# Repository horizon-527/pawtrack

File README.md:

# PawTrack

宠物独立联网定位器 + 微信小程序。目标：项圈设备获取 GNSS 位置，通过 4G 回传，主人在微信中查看位置和运动轨迹。

**当前状态：软件与可编译硬件原型已建立；尚未完成实体板定位、真实微信登录、公网部署及佩戴验收。**

新增 [定制硬件 EVT-A1 交厂包](hardware/custom/evt-a1/README.md)：可编辑原理图、四层布线 PCB、BOM、Gerber/钻孔/贴片坐标、外壳 STL、Air780EGH 应用和36项实体验收表。ERC/DRC/原理图与 PCB 一致性检查通过；制造发布状态 **HOLD**，先由方案商关闭引脚资料矛盾、电源和叠层评审，再做两台样机。该方案由厂商代采、贴片、装配，详见 [交厂说明](hardware/custom/evt-a1/factory-handoff.md)。

## 已实现
- 微信小程序地图、实时刷新、按日期查询轨迹、坐标转换、轨迹缺口分段。
- 微信登录接口、设备绑定、用户设备隔离、在线/定位过期状态、寻找模式请求与设备确认。
- FastAPI + SQLite 服务，独立设备密钥、一次性绑定码、会话过期/撤销、限流、数据删除与30天保留。
- ESP-IDF v5.4.2 固件：SIM7670G AT通信、GNSS读取、HTTPS上传、NVS缓存、模式心跳；ESP32-S3构建通过。
- 设备模拟器、GNSS日志回放、设备初始化、备份恢复工具、Docker/Caddy配置、CI。

## 先体验小程序
微信开发者工具导入 `miniprogram/`。默认使用游客 AppID 和模拟路线，明确标记演示数据。演示无需真实硬件、服务器或微信登录。
正式接入必须替换 AppID 和 HTTPS 服务地址；项目未使用其他项目的 AppID 或密钥。

## 本地运行与验证
```sh
python3 -m venv work/venv
work/venv/bin/pip install -r requirements.lock.txt
work/venv/bin/python tools/check.py
work/venv/bin/uvicorn server.production:create_app --factory --host 127.0.0.1 --port 8788 --no-access-log
```
不配置真实微信密钥时，登录返回“尚未配置”，不会伪造用户身份。接口测试使用隔离的微信响应替身，不代表真实微信认证通过。

## 文档入口
- **[从采购到真实定位：逐步操作指南](docs/getting-started.md)**
- [完整采购和组装](hardware/procurement-and-assembly.md)
- [真机实测与验收表](docs/acceptance.md)
- [常见问题排查](docs/troubleshooting.md)
- [实施与验收计划](docs/plan.md)
- [硬件采购路线](hardware/README.md)
- [固件配置与烧录](firmware/espidf/README.md)
- [服务部署和备份](deploy/README.md)
- [API v1](docs/api-v1.md)
- [测试记录与待办](docs/verification.md)
- [上线门槛](docs/release.md)
- [开源许可](THIRD_PARTY.md)

## 最新完善
支持继续添加另一只宠物，位置5秒轮询/轨迹30秒缓存刷新、手动刷新、历史轨迹终点、会话过期处理；已在微信开发者工具运行并修复坐标库兼容和地图标记渲染问题。
提供独立真机项目配置工具、部署健康/TLS检查、每日自动备份与7天清理、离线恢复、私有TLS负例测试服务。正式微信登录、实体GNSS/4G与佩戴仍须按验收表测试。

## 原始本地原型
`python3 server/app.py`（8787）与 `python3 tools/simulate.py` 为早期本机开发原型；仅监听本机，固定开发令牌，不可公网部署。它的数据库与 v1 独立。
小程序 `config.js` 可切换 apiMode=prototype 且 apiBase 改为8787进行旧版联调；正式流程保持v1。

## 完成产品仍需的外部条件
实体开发板与SIM；小程序AppID/Secret；可部署的服务器/域名；实际定位、TLS证书验证、功耗及佩戴测试。开发板用于桌面验证，不能直接作为宠物项圈成品。

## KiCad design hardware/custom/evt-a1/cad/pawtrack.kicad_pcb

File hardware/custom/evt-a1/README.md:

# PawTrack 定制硬件 EVT-A1

这是一套**工程样机设计**，发布状态为 **HOLD / 尚未获准制造和佩戴使用**。文件可交给国内硬件方案商作原理图评审、DFM 和整机报价；只有完成下面的确认与样机验收，才能把它称为能使用的定位器。没有采购、投板、实体烧录或实测数据。

固定方案：Air780EGH 4G/GNSS OpenCPU + BQ24074 充电及电源路径 + TPS63070 3.8V 稳压 + 带保护板和温度传感器的单节电池。没有额外 ESP32。此板运行 `firmware/` 的 LuatOS 脚本，**不能刷已有的 ESP32 固件**。数据接入仓库的 API v1 和微信小程序。

| 内容 | 文件 | 能说明什么 |
|---|---|---|
| 自定义原理图、布线 PCB、项目库 | `cad/pawtrack.kicad_sch`、`.kicad_pcb`、`.kicad_pro` | KiCad 10 可编辑；不是开发板接线图 |
| BOM、Gerber、钻孔、贴片坐标 | `manufacturing/` | 工程评审/报价输出；默认不贴 RF 调谐电容 |
| 原生检查与独立连接核对 | `reports/` | 电脑上的几何和连接检查；不证明射频、电源和电池合格 |
| 外壳实体、参数源、尺寸图 | `enclosure/` | STL 可作 PA12 打印询价；装配、耐拉和防水未实测 |
| 模组应用及测试 | `firmware/` | 上传协议和队列可在电脑测试；模组 API、TLS、ADC 要在样机验证 |
| 交厂与验收 | `factory-handoff.md`、`acceptance.csv` | 先评审、后样机、通过后再交付，附记录表 |

PCB 为 64×46mm、四层、目标厚度 1.0mm。外壳主体 74×56×27mm，含绑带耳总长 90mm，接受 20mm 织带。**这是保留调试余量的原型，重量尚未测量，不能当作小型猫狗项圈成品。**先用人持设备和等重空壳测试，再决定佩戴对象和下一版尺寸。

先读 `factory-handoff.md`。请勿只把 Gerber 发给 PCB 厂、跳过电路评审。制板贴片服务不自动包含电池选型、射频调试、固件联调和整机验收。

原理图使用嵌入式、自带库的编号符号，保留真实封装焊盘号码及供电/输入/输出类型，连接由网标完成。设计源 `scripts/design.py` 会重建未布线 PCB，**不要在已布线文件上无意运行覆盖**；修改设计后必须重布线、重新导出并重做所有检查。

检查证据见 [verification.md](reports/verification.md)，器件核对及未关闭问题见 [design-review.md](reports/design-review.md)，重新导出说明见 [scripts/README.md](scripts/README.md)。制造包的 SHA256 清单在 `files.sha256.json`；`python scripts/verify.py --manifest` 可核验交付文件是否变动。若改版，先重做原生检查与导出，最后运行 `python scripts/seal.py` 更新清单。

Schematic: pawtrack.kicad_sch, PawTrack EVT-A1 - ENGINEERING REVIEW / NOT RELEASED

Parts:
C1, C2: 4.7uF; C_0603_1608Metric; MPN GRM188R61A475KE15D
C3, C4, C7, C8: 22uF; C_0805_2012Metric; MPN GRM21BR60J226ME39L
C5, C6, C9, C11, C12, C13, C20: 100nF; C_0603_1608Metric; MPN GRM188R71C104KA01D
C10: 1uF; C_0603_1608Metric; MPN GRM188R61A105KA61D
C14: 100uF 6.3V; CP_EIA-3528-21_Kemet-B; MPN T520B107M006ATE070
C15: 33pF; C_0603_1608Metric; MPN GRM1885C1H330JA01D
C16, C17, C18, C19: DNP tuning; C_0603_1608Metric; MPN DNP tuning; not fitted
D1, D2: ESD; D_SOD-882; MPN PESD5V0S1UL,315
D3, D4, D5: ESD; D_SOD-882; MPN PESD3V3S1UL,315
H1, H2, H3, H4: M2 clearance; MountingHole_2.2mm_M2; MPN PCB feature; not fitted
J1: USB-C; USB_C_Receptacle_HRO_TYPE-C-31-M-12; MPN TYPE-C-31-M-12
J2: Protected LiPo+NTC; JST_PH_B3B-PH-SM4-TB_1x03-1MP_P2.00mm_Vertical; MPN B3B-PH-SM4-TB(LF)(SN)
J3: LTE 50ohm; U.FL_Hirose_U.FL-R-SMT-1_Vertical; MPN U.FL-R-SMT-1(10)
J4: GNSS active; U.FL_Hirose_U.FL-R-SMT-1_Vertical; MPN U.FL-R-SMT-1(10)
J5: nanoSIM; nanoSIM_Hinged_CUI_NSIM-2-C; MPN NSIM-2-C
L1: 1uH 5.4A; XFL4020; MPN XFL4020-102MEC
L2: 47nH; L_0603_1608Metric; MPN 0603HP-47NXJRW
Q1: 2N7002; SOT-23; MPN 2N7002,215
R1, R2: 5.1k; R_0603_1608Metric; MPN RC0603FR-075K1L
R3: 2.55k; R_0603_1608Metric; MPN RC0603FR-072K55L
R4: 3.24k; R_0603_1608Metric; MPN RC0603FR-073K24L
R5: 750k; R_0603_1608Metric; MPN RC0603FR-07750KL
R6: 200k; R_0603_1608Metric; MPN RC0603FR-07200KL
R7, R9, R16, R17: 100k; R_0603_1608Metric; MPN RC0603FR-07100KL
R8: 330k; R_0603_1608Metric; MPN RC0603FR-07330KL
R10, R11, R12: 22; R_0603_1608Metric; MPN RC0603FR-0722RL
R13, R14: 0; R_0603_1608Metric; MPN RC0603JR-070RL
R15: 10k; R_0603_1608Metric; MPN RC0603FR-0710KL
R18: 1k; R_0603_1608Metric; MPN RC0603FR-071KL
R19: 3.3M; R_0603_1608Metric; MPN RC0603FR-073M3L
R20: 1M; R_0603_1608Metric; MPN RC0603FR-071ML
SW1: POWER KEY; SW_SPST_SKQG_WithoutStem; MPN SKQGAKE010
SW2: RESET; SW_SPST_SKQG_WithoutStem; MPN SKQGAKE010
TP1: VDD_EXT; TestPoint_Pad_D1.0mm; MPN PCB pad; not fitted
TP2: USB_BOOT; TestPoint_Pad_D1.0mm; MPN PCB pad; not fitted
TP3: DBG_RX; TestPoint_Pad_D1.0mm; MPN PCB pad; not fitted
TP4: DBG_TX; TestPoint_Pad_D1.0mm; MPN PCB pad; not fitted
TP5: GND; TestPoint_Pad_D1.0mm; MPN PCB pad; not fitted
TP6: SYS; TestPoint_Pad_D1.0mm; MPN PCB pad; not fitted
TP7: V_MODEM; TestPoint_Pad_D1.0mm; MPN PCB pad; not fitted
TP8: REG_EN; TestPoint_Pad_D1.0mm; MPN PCB pad; not fitted
TP9: BAT; TestPoint_Pad_D1.0mm; MPN PCB pad; not fitted
U1: Air780EGH; Air780EGH_109; MPN Air780EGH
U2: BQ24074RGTR; WQFN-16-1EP_3x3mm_P0.5mm_EP1.68x1.68mm; MPN BQ24074RGTR
U3: TPS63070RNMR; TPS63070_RNM0015A; MPN TPS63070RNMR

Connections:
BAT: C2.1 (BAT), J2.1 (BAT), R8.1 (BAT), TP9.1, U2.2 (BAT), U2.3 (BAT)
BAT_SENSE: C13.1 (BAT_SENSE), R8.2 (BAT_SENSE), R9.1 (BAT_SENSE), U1.9 (BAT_SENSE)
CC1: J1.A5 (CC1), R1.1 (CC1)
CC2: J1.B5 (CC2), R2.1 (CC2)
CHG_CTRL: R18.1 (CHG_CTRL), U1.16 (CHG_CTRL)
CHG_DISABLE: Q1.3 (CHG_DISABLE), R16.2 (CHG_DISABLE), U2.4 (CHG_DISABLE)
CHG_GATE: Q1.1 (CHG_GATE), R17.1 (CHG_GATE), R18.2 (CHG_GATE)
DBG_RX: TP3.1, U1.38 (DBG_RX)
DBG_TX: TP4.1, U1.39 (DBG_TX)
FB: R5.2 (FB), R6.1 (FB), U3.5 (FB)
GND: C1.2 (GND), C2.2 (GND), C3.2 (GND), C4.2 (GND), C5.2 (GND), C6.2 (GND), C7.2 (GND), C8.2 (GND), C9.2 (GND), C10.2 (GND), C11.2 (GND), C12.2 (GND), C13.2 (GND), C14.2 (GND), C16.2 (GND), C17.2 (GND), C18.2 (GND), C19.2 (GND), C20.2 (GND), D1.2 (GND), D2.2 (GND), D3.2 (GND), D4.2 (GND), D5.2 (GND), J1.A1 (GND), J1.A12 (GND), J1.B1 (GND), J1.B12 (GND), J1.SH (GND), J2.2 (GND), J2.MP (GND), J3.2 (GND), J4.2 (GND), J5.5 (GND), J5.SH (GND), Q1.2 (GND), R1.2 (GND), R2.2 (GND), R3.2 (GND), R4.2 (GND), R6.2 (GND), R9.2 (GND), R17.2 (GND), R20.2 (GND), SW1.2 (GND), SW2.2 (GND), TP5.1, U1.1 (GND), U1.10 (GND), U1.27 (GND), U1.34 (GND), U1.36 (GND), U1.37 (GND), U1.40 (GND), U1.41 (GND), U1.45 (GND), U1.46 (GND), U1.47 (GND), U1.48 (GND), U1.70 (GND), U1.71 (GND), U1.72 (GND), U1.73 (GND), U1.88 (GND), U1.89 (GND), U1.90 (GND), U1.91 (GND), U1.92 (GND), U1.93 (GND), U1.94 (GND), U1.95 (GND), U1.103 (GND), U2.5 (GND), U2.8 (GND), U2.17 (GND), U3.1 (GND), U3.4 (GND), U3.10 (GND), U3.15 (GND)
GNSS_BIAS: L2.1 (GNSS_BIAS), R14.2 (GNSS_BIAS)
GNSS_FEED: C15.2 (GNSS_FEED), C19.1 (GNSS_FEED), J4.1 (GNSS_FEED), L2.2 (GNSS_FEED)
GNSS_IN: C15.1 (GNSS_IN), C18.1 (GNSS_IN), U1.2 (GNSS_IN)
GNSS_VDD: C11.1 (GNSS_VDD), R14.1 (GNSS_VDD), U1.98 (GNSS_VDD)
ILIM: R4.1 (ILIM), U2.12 (ILIM)
ISET: R3.1 (ISET), U2.16 (ISET)
LTE_FEED: C17.1 (LTE_FEED), J3.1 (LTE_FEED), R13.2 (LTE_FEED)
LTE_IN: C16.1 (LTE_IN), R13.1 (LTE_IN), U1.35 (LTE_IN)
NTC: J2.3 (NTC), R19.1 (NTC), U2.1 (NTC)
PWRKEY: SW1.1 (PWRKEY), U1.7 (PWRKEY)
REG_EN: R7.2 (REG_EN), TP8.1, U3.14 (REG_EN)
RESET_N: SW2.1 (RESET_N), U1.15 (RESET_N)
SIM_CLK: D5.1 (SIM_CLK), J5.3 (SIM_CLK), R12.2 (SIM_CLK)
SIM_CLK_M: R12.1 (SIM_CLK_M), U1.13 (SIM_CLK_M)
SIM_IO: D3.1 (SIM_IO), J5.7 (SIM_IO), R10.2 (SIM_IO), R15.2 (SIM_IO)
SIM_IO_M: R10.1 (SIM_IO_M), U1.11 (SIM_IO_M)
SIM_RST: D4.1 (SIM_RST), J5.2 (SIM_RST), R11.2 (SIM_RST)
SIM_RST_M: R11.1 (SIM_RST_M), U1.12 (SIM_RST_M)
SIM_VDD: C12.1 (SIM_VDD), J5.1 (SIM_VDD), R15.1 (SIM_VDD), U1.14 (SIM_VDD)
SW1: L1.1 (SW1), U3.11 (SW1)
SW2: L1.2 (SW2), U3.9 (SW2)
SYS: C3.1 (SYS), C4.1 (SYS), C5.1 (SYS), R7.1 (SYS), TP6.1, U2.10 (SYS), U2.11 (SYS), U3.12 (SYS), U3.13 (SYS)
TS_SENSE: C20.1 (TS_SENSE), R19.2 (TS_SENSE), R20.1 (TS_SENSE), U1.96 (TS_SENSE)
USB_BOOT: TP2.1, U1.82 (USB_BOOT)
USB_DM: D2.1 (USB_DM), J1.A7 (USB_DM), J1.B7 (USB_DM), U1.60 (USB_DM)
USB_DP: D1.1 (USB_DP), J1.A6 (USB_DP), J1.B6 (USB_DP), U1.59 (USB_DP)
VAUX: C6.1 (VAUX), U3.3 (VAUX)
VBUS: C1.1 (VBUS), J1.A4 (VBUS), J1.A9 (VBUS), J1.B4 (VBUS), J1.B9 (VBUS), R16.1 (VBUS), U1.61 (VBUS), U2.6 (VBUS), U2.13 (VBUS)
VDD_EXT: TP1.1, U1.24 (VDD_EXT)
V_MODEM: C7.1 (V_MODEM), C8.1 (V_MODEM), C9.1 (V_MODEM), C10.1 (V_MODEM), C14.1 (V_MODEM), R5.1 (V_MODEM), TP7.1, U1.42 (V_MODEM), U1.43 (V_MODEM), U3.7 (V_MODEM), U3.8 (V_MODEM)

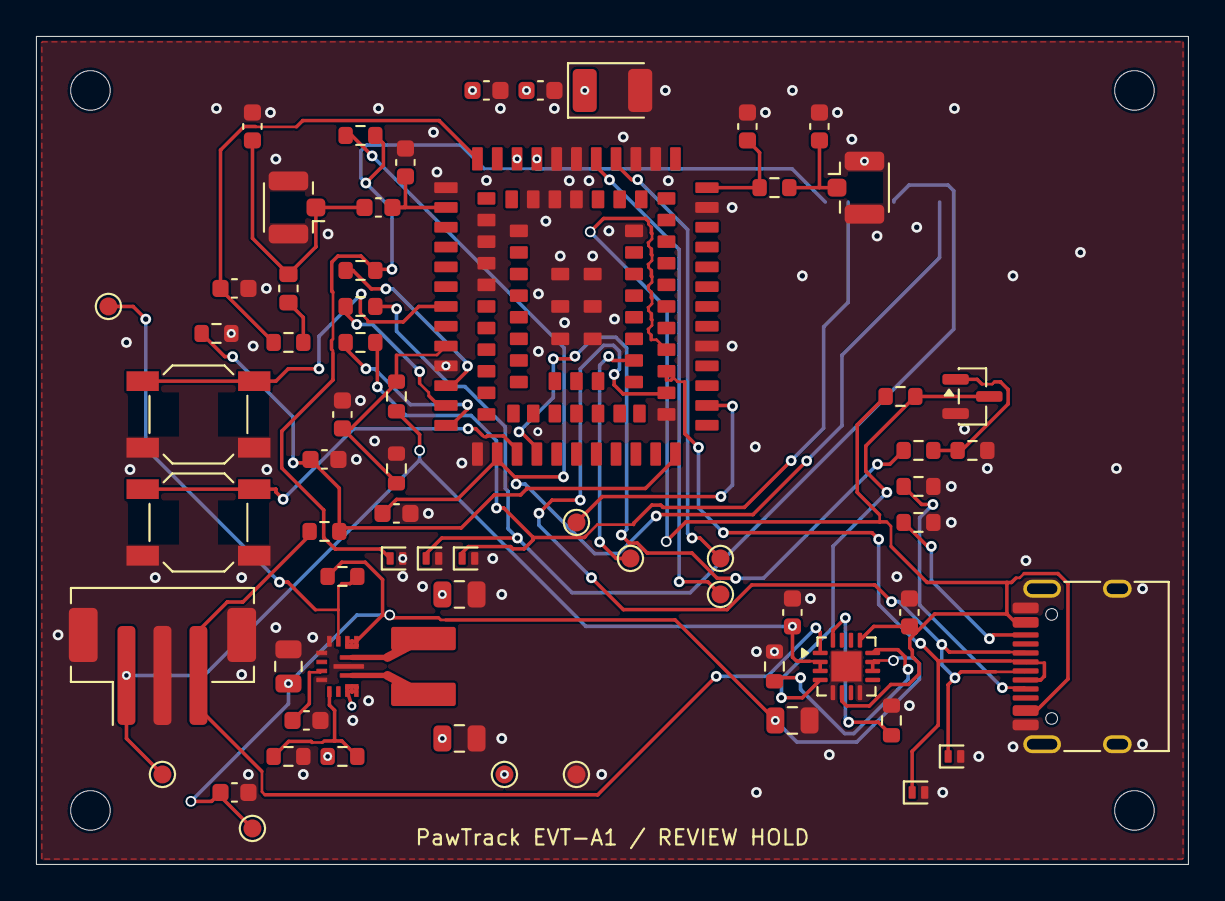
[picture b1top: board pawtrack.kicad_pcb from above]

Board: 4 copper layers, 64.0 x 46.0 mm, 71 parts (1 on the bottom side), 41 nets.

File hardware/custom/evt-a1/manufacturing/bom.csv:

Reference,Value,MPN,Footprint,Populate,Side,Notes
U1,Air780EGH,Air780EGH,PawTrack:Air780EGH_109,1,F,Pin 2/103 document conflict; factory confirmation HOLD
U2,BQ24074RGTR,BQ24074RGTR,Package_DFN_QFN:WQFN-16-1EP_3x3mm_P0.5mm_EP1.68x1.68mm,1,F,
U3,TPS63070RNMR,TPS63070RNMR,PawTrack:TPS63070_RNM0015A,1,F,
L1,1uH 5.4A,XFL4020-102MEC,PawTrack:XFL4020,1,F,Isat>=5.4A; DCR<=15mohm; no unreviewed substitute
J1,USB-C,TYPE-C-31-M-12,Connector_USB:USB_C_Receptacle_HRO_TYPE-C-31-M-12,1,F,
J2,Protected LiPo+NTC,B3B-PH-SM4-TB(LF)(SN),Connector_JST:JST_PH_B3B-PH-SM4-TB_1x03-1MP_P2.00mm_Vertical,1,F,"Pin1 BAT+, pin2 BAT-, pin3 NTC to BAT-; manufacturer must key-match harness"
J3,LTE 50ohm,U.FL-R-SMT-1(10),Connector_Coaxial:U.FL_Hirose_U.FL-R-SMT-1_Vertical,1,F,
J4,GNSS active,U.FL-R-SMT-1(10),Connector_Coaxial:U.FL_Hirose_U.FL-R-SMT-1_Vertical,1,F,
J5,nanoSIM,NSIM-2-C,Connector_Card:nanoSIM_Hinged_CUI_NSIM-2-C,1,B,No hot insertion; factory verify exact connector stock drawing
SW1,POWER KEY,SKQGAKE010,Button_Switch_SMD:SW_SPST_SKQG_WithoutStem,1,F,
SW2,RESET,SKQGAKE010,Button_Switch_SMD:SW_SPST_SKQG_WithoutStem,1,F,
C1,4.7uF,GRM188R61A475KE15D,Capacitor_SMD:C_0603_1608Metric,1,F,
C2,4.7uF,GRM188R61A475KE15D,Capacitor_SMD:C_0603_1608Metric,1,F,
C3,22uF,GRM21BR60J226ME39L,Capacitor_SMD:C_0805_2012Metric,1,F,
C4,22uF,GRM21BR60J226ME39L,Capacitor_SMD:C_0805_2012Metric,1,F,
C5,100nF,GRM188R71C104KA01D,Capacitor_SMD:C_0603_1608Metric,1,F,
C6,100nF,GRM188R71C104KA01D,Capacitor_SMD:C_0603_1608Metric,1,F,
C7,22uF,GRM21BR60J226ME39L,Capacitor_SMD:C_0805_2012Metric,1,F,
C8,22uF,GRM21BR60J226ME39L,Capacitor_SMD:C_0805_2012Metric,1,F,
C9,100nF,GRM188R71C104KA01D,Capacitor_SMD:C_0603_1608Metric,1,F,
C10,1uF,GRM188R61A105KA61D,Capacitor_SMD:C_0603_1608Metric,1,F,
C11,100nF,GRM188R71C104KA01D,Capacitor_SMD:C_0603_1608Metric,1,F,
C12,100nF,GRM188R71C104KA01D,Capacitor_SMD:C_0603_1608Metric,1,F,
C13,100nF,GRM188R71C104KA01D,Capacitor_SMD:C_0603_1608Metric,1,F,
C14,100uF 6.3V,T520B107M006ATE070,Capacitor_Tantalum_SMD:CP_EIA-3528-21_Kemet-B,1,F,Polymer ESR70mohm; polarity positive pad1
R1,5.1k,RC0603FR-075K1L,Resistor_SMD:R_0603_1608Metric,1,F,
R2,5.1k,RC0603FR-075K1L,Resistor_SMD:R_0603_1608Metric,1,F,
R3,2.55k,RC0603FR-072K55L,Resistor_SMD:R_0603_1608Metric,1,F,
R4,3.24k,RC0603FR-073K24L,Resistor_SMD:R_0603_1608Metric,1,F,
R5,750k,RC0603FR-07750KL,Resistor_SMD:R_0603_1608Metric,1,F,
R6,200k,RC0603FR-07200KL,Resistor_SMD:R_0603_1608Metric,1,F,
R7,100k,RC0603FR-07100KL,Resistor_SMD:R_0603_1608Metric,1,F,
R8,330k,RC0603FR-07330KL,Resistor_SMD:R_0603_1608Metric,1,F,
R9,100k,RC0603FR-07100KL,Resistor_SMD:R_0603_1608Metric,1,F,
R10,22,RC0603FR-0722RL,Resistor_SMD:R_0603_1608Metric,1,F,
R11,22,RC0603FR-0722RL,Resistor_SMD:R_0603_1608Metric,1,F,
R12,22,RC0603FR-0722RL,Resistor_SMD:R_0603_1608Metric,1,F,
R13,0,RC0603JR-070RL,Resistor_SMD:R_0603_1608Metric,1,F,
R14,0,RC0603JR-070RL,Resistor_SMD:R_0603_1608Metric,1,F,
R15,10k,RC0603FR-0710KL,Resistor_SMD:R_0603_1608Metric,1,F,
C15,33pF,GRM1885C1H330JA01D,Capacitor_SMD:C_0603_1608Metric,1,F,
L2,47nH,0603HP-47NXJRW,Inductor_SMD:L_0603_1608Metric,1,F,
C16,DNP tuning,DNP tuning,Capacitor_SMD:C_0603_1608Metric,0,F,RF engineer tune only; default NOT fitted
C17,DNP tuning,DNP tuning,Capacitor_SMD:C_0603_1608Metric,0,F,RF engineer tune only; default NOT fitted
C18,DNP tuning,DNP tuning,Capacitor_SMD:C_0603_1608Metric,0,F,RF engineer tune only; default NOT fitted
C19,DNP tuning,DNP tuning,Capacitor_SMD:C_0603_1608Metric,0,F,RF engineer tune only; default NOT fitted
D1,ESD,"PESD5V0S1UL,315",Diode_SMD:D_SOD-882,1,F,
D2,ESD,"PESD5V0S1UL,315",Diode_SMD:D_SOD-882,1,F,
D3,ESD,"PESD3V3S1UL,315",Diode_SMD:D_SOD-882,1,F,
D4,ESD,"PESD3V3S1UL,315",Diode_SMD:D_SOD-882,1,F,
D5,ESD,"PESD3V3S1UL,315",Diode_SMD:D_SOD-882,1,F,
TP1,VDD_EXT,PCB pad,TestPoint:TestPoint_Pad_D1.0mm,0,F,DNP/no component; factory jig access
TP2,USB_BOOT,PCB pad,TestPoint:TestPoint_Pad_D1.0mm,0,F,DNP/no component; factory jig access
TP3,DBG_RX,PCB pad,TestPoint:TestPoint_Pad_D1.0mm,0,F,DNP/no component; factory jig access
TP4,DBG_TX,PCB pad,TestPoint:TestPoint_Pad_D1.0mm,0,F,DNP/no component; factory jig access
TP5,GND,PCB pad,TestPoint:TestPoint_Pad_D1.0mm,0,F,DNP/no component; factory jig access
TP6,SYS,PCB pad,TestPoint:TestPoint_Pad_D1.0mm,0,F,DNP/no component; factory jig access
TP7,V_MODEM,PCB pad,TestPoint:TestPoint_Pad_D1.0mm,0,F,DNP/no component; factory jig access
TP8,REG_EN,PCB pad,TestPoint:TestPoint_Pad_D1.0mm,0,F,DNP/no component; factory jig access
TP9,BAT,PCB pad,TestPoint:TestPoint_Pad_D1.0mm,0,F,DNP/no component; factory jig access
H1,M2 clearance,PCB feature,MountingHole:MountingHole_2.2mm_M2,0,F,
H2,M2 clearance,PCB feature,MountingHole:MountingHole_2.2mm_M2,0,F,
H3,M2 clearance,PCB feature,MountingHole:MountingHole_2.2mm_M2,0,F,
H4,M2 clearance,PCB feature,MountingHole:MountingHole_2.2mm_M2,0,F,
Q1,2N7002,"2N7002,215",Package_TO_SOT_SMD:SOT-23,1,F,
R16,100k,RC0603FR-07100KL,Resistor_SMD:R_0603_1608Metric,1,F,
R17,100k,RC0603FR-07100KL,Resistor_SMD:R_0603_1608Metric,1,F,
R18,1k,RC0603FR-071KL,Resistor_SMD:R_0603_1608Metric,1,F,
R19,3.3M,RC0603FR-073M3L,Resistor_SMD:R_0603_1608Metric,1,F,
R20,1M,RC0603FR-071ML,Resistor_SMD:R_0603_1608Metric,1,F,
C20,100nF,GRM188R71C104KA01D,Capacitor_SMD:C_0603_1608Metric,1,F,

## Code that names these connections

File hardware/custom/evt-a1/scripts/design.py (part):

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add('U3','TPS63070RNMR','PawTrack:TPS63070_RNM0015A',{1:'GND',2:None,3:'VAUX',4:'GND',5:'FB',7:'V_MODEM',8:'V_MODEM',9:'SW2',10:'GND',11:'SW1',12:'SYS',13:'SYS',14:'REG_EN',15:'GND'},17,35)
add('L1','1uH 5.4A','PawTrack:XFL4020',{1:'SW1',2:'SW2'},21.5,35,90,'XFL4020-102MEC',note='Isat>=5.4A; DCR<=15mohm; no unreviewed substitute')
add('J1','USB-C','Connector_USB:USB_C_Receptacle_HRO_TYPE-C-31-M-12',{'A1':'GND','A4':'VBUS','A5':'CC1','A6':'USB_DP','A7':'USB_DM','A8':None,'A9':'VBUS','A12':'GND','B1':'GND','B4':'VBUS','B5':'CC2','B6':'USB_DP','B7':'USB_DM','B8':None,'B9':'VBUS','B12':'GND','SH':'GND'},59,35,90,'TYPE-C-31-M-12')
add('J2','Protected LiPo+NTC','Connector_JST:JST_PH_B3B-PH-SM4-TB_1x03-1MP_P2.00mm_Vertical',{1:'BAT',2:'GND',3:'NTC','MP':'GND'},7,35,0,'B3B-PH-SM4-TB(LF)(SN)',note='Pin1 BAT+, pin2 BAT-, pin3 NTC to BAT-; manufacturer must key-match harness')
add('J3','LTE 50ohm','Connector_Coaxial:U.FL_Hirose_U.FL-R-SMT-1_Vertical',{1:'LTE_FEED',2:'GND'},46,8.4,0,'U.FL-R-SMT-1(10)')
add('J4','GNSS active','Connector_Coaxial:U.FL_Hirose_U.FL-R-SMT-1_Vertical',{1:'GNSS_FEED',2:'GND'},14,9.5,180,'U.FL-R-SMT-1(10)')
add('J5','nanoSIM','Connector_Card:nanoSIM_Hinged_CUI_NSIM-2-C',{1:'SIM_VDD',2:'SIM_RST',3:'SIM_CLK',5:'GND',6:None,7:'SIM_IO','SH':'GND','CD':None},47,16,0,'NSIM-2-C',side='B',note='No hot insertion; factory verify exact connector stock drawing')
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    pos=loc(ref,num);v=p.PCB_VIA(b);v.SetPosition(pos);v.SetWidth(mm(.5));v.SetDrill(mm(.25));v.SetLayerPair(p.F_Cu,p.B_Cu);v.SetViaType(p.VIATYPE_THROUGH);v.SetNet(netmap[net]);b.Add(v)
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v=p.PCB_VIA(b);v.SetPosition(pt(17.525,37.2));v.SetWidth(mm(.5));v.SetDrill(mm(.25));v.SetLayerPair(p.F_Cu,p.B_Cu);v.SetViaType(p.VIATYPE_THROUGH);v.SetNet(netmap['V_MODEM']);b.Add(v)
track('V_MODEM',loc('U3',7),v.GetPosition(),.2)
# Ground planes are filled only after routing; reserve inner1 continuous GND.
for layer in [p.F_Cu,p.In1_Cu,p.In2_Cu,p.B_Cu]:
    z=p.ZONE(b);z.SetLayer(layer);z.SetNet(netmap['V_MODEM' if layer==p.In2_Cu else 'GND']);z.SetLocalClearance(mm(.2));z.SetPadConnection(p.ZONE_CONNECTION_FULL);z.SetMinThickness(mm(.15))
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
